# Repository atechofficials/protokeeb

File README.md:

<picture>
 <source media="(prefers-color-scheme: dark)" srcset="Images/protokeeb_logo/protokeeb_logo_white.png">
 <source media="(prefers-color-scheme: light)" srcset="Images/protokeeb_logo/protokeeb_logo_black.png">
 
</picture>

# Protokeeb

### Overview

Protokeeb is a 16-key (4 x 4) keyboard/numpad/macropad/MIDI device designed by A-Tech Officials. It is ideal for those looking to get started with custom keyboards and open-source keyboard firmware. The PCB is based on a Raspberry Pi Pico development board, making it perfect for developers and enthusiasts eager to explore the world of custom keyboards and firmware.

## Features

- Per-key south-facing ARGB (WS2812B-2020) backlight LED.
- All anti-ghosting keys. It's a Mechanical Keyboard. Duh.
- N-Key Rollover
- On-board ESD/EMI protection.
- Rotary Encoder with push button.
- USB Type-C port. Not a feature anymore in 2024. #NoMoreMicroUSB
- Dedicated Bootselect and Reset Button for easy bootloader access.
- Supports various RP2040-based development boards that have similar SMD footprint and pinout to a Raspberry Pi Pico.
- 2MB/4MB flash storage for comprehensive keyboard firmware.
- Compatible with QMK, KMK, and ZMK keyboard firmware.
- Support both sandwich style/layered case or 3D-printed cases.

## Supported Dev Boards

- Raspberry Pi Pico
- Raspberry Pi Pico W
- Waveshare RP2040-Plus

## Getting Started

You can get started with Protokeeb hardware in two ways:

- **Option 1**: Order a fully assembled/soldered PCB from [A-Tech Officials](https://atechofficials.com/protokeeb) (Work-in-progress).
- **Option 2**: Download the Gerber and necessary files to order the PCB from your local or preferred PCB fabrication company and source all required electronic components yourself.

**Option 1** is a straightforward plug-and-play option, as each Protokeeb board comes pre-flashed with QMK firmware and a default keymap, allowing easy customization without worrying about the electronics.

**Option 2** is a DIY approach with detailed instructions provided for almost every step, ideal for those who want to immerse themselves in the learning, development, and customization aspects of custom keyboards.

> [!NOTE]
> Option 2 is not recommended for absolute beginners in electronics, as it requires specific skills and basic electronics knowledge, including proficient SMD soldering skills.

For detailed assembly instructions, follow this guide: [Assembly Instructions](assembly_instructions.md)

## License

This project is licensed under the MIT License. See the [LICENSE](LICENSE) file for details.

## Contributing

Contributions are welcome! Please fork this repository and submit a pull request with your changes.

## Support

For any issues or questions, please open an issue on GitHub.

## Acknowledgements

Thanks to the open-source community for their support and contributions.

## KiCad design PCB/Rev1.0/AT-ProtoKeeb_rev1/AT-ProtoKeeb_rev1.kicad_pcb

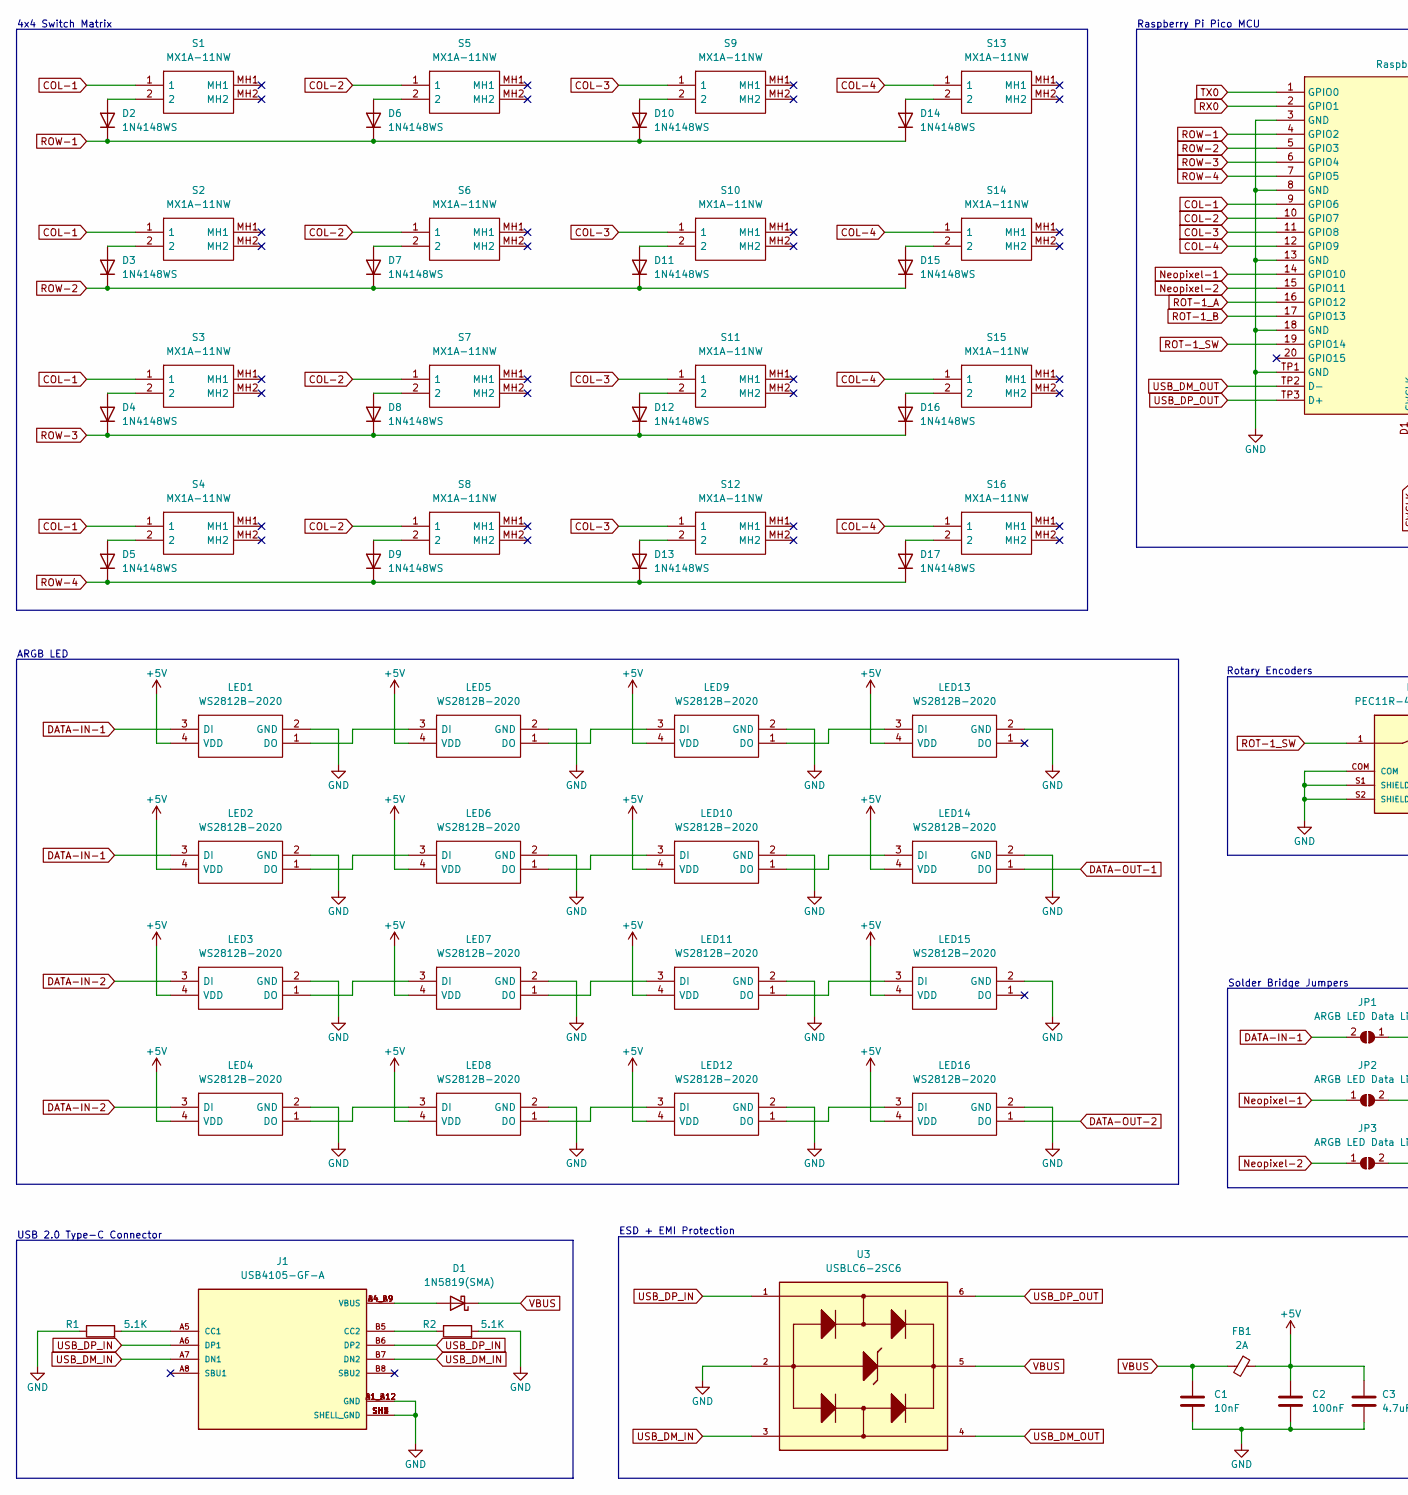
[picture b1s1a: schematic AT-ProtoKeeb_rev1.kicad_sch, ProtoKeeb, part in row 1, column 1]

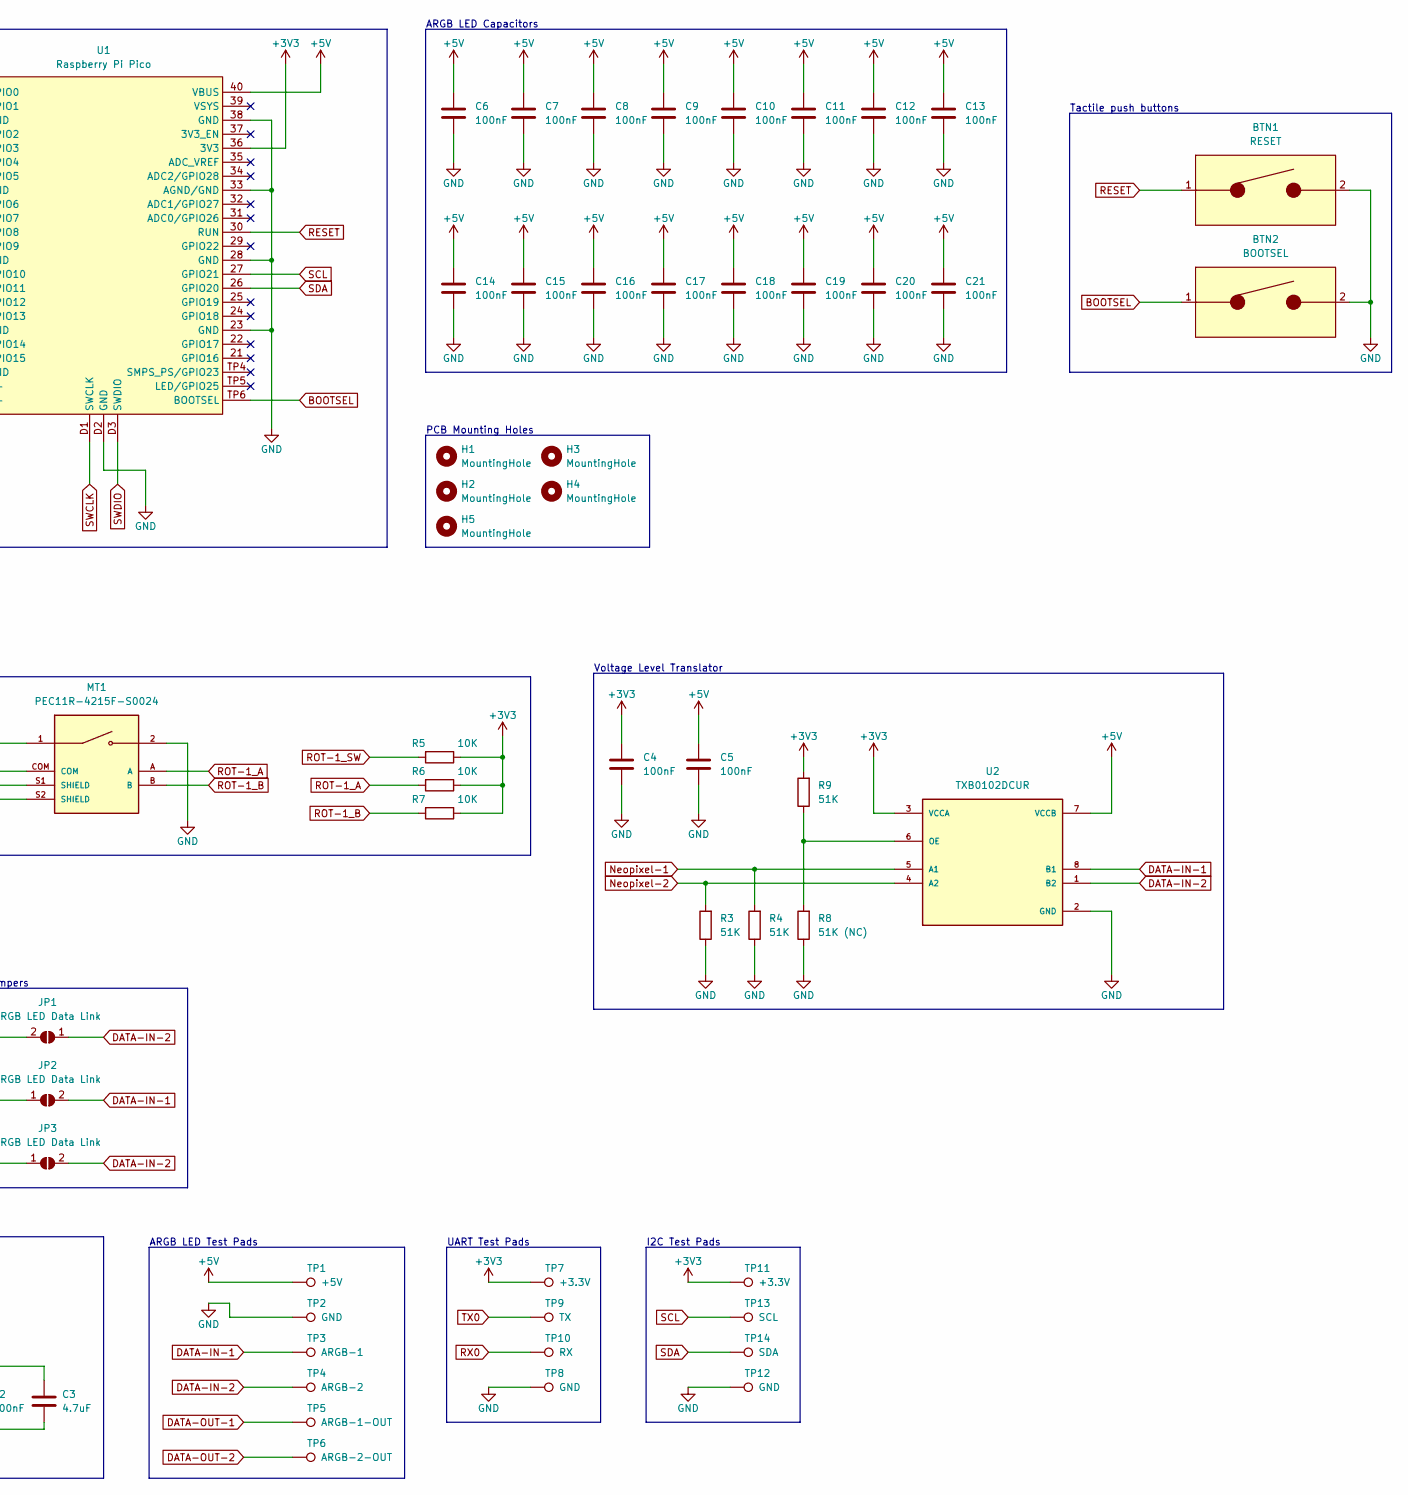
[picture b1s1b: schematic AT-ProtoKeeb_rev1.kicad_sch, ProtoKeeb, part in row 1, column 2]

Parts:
BTN1: RESET; 4982; Mouser Part Number 653-B3U-1000PM
BTN2: BOOTSEL; 4982; Mouser Part Number 653-B3U-1000PM
C1: 10nF; C_0603_1608Metric; Mouser Part Number 603-CC603KRX7R9BB103
C2, C4, C5, C6, C7, C8, C9, C10, C11, C12, C13, C14, C15, C16, C17, C18, C19, C20, C21: 100nF; C_0603_1608Metric; Mouser Part Number 81-GCJ188R71H104KA2D
C3: 4.7uF; C_0603_1608Metric; Mouser Part Number 81-GRM188Z71C475KE1D
D1: 1N5819(SMA); D_SMA; Mouser Part Number 512-SS14
D2, D3, D4, D5, D6, D7, D8, D9, D10, D11, D12, D13, D14, D15, D16, D17: 1N4148WS; D_SOD-323; Mouser Part Number 512-1N4148WS
FB1: 2A; L_0603_1608Metric; Mouser Part Number 810-MPZ1608S221ATA00
H1, H2, H3, H4, H5: MountingHole; MountingHole_2.7mm_M2.5_ISO7380
J1: USB4105-GF-A; GCT_USB4105-GF-A; PARTREV B3; Mouser Part Number 640-USB4105-GF-A
JP1, JP2, JP3: ARGB LED Data Link; SolderJumper-2_P1.3mm_Open_TrianglePad1.0x1.5mm
LED1, LED2, LED3, LED4, LED5, LED6, LED7, LED8, LED9, LED10, LED11, LED12, LED13, LED14, LED15, LED16: WS2812B-2020; WS2812B2020; Manufacturer_Part_Number WS2812B-2020; Mouser Part Number 485-4684
MT1: PEC11R-4215F-S0024; XDCR_PEC11R-4215F-S0024; PARTREV Rev. 09/19; Mouser Part Number 652-PEC11R-4215F-S24
R1, R2: 5.1K; R_0603_1608Metric; Mouser Part Number 603-RC0603FR-075K1L
R3, R4, R9: 51K; R_0603_1608Metric; Mouser Part Number 603-RC0603FR-0751KL
R5, R6, R7: 10K; R_0603_1608Metric; Mouser Part Number 603-RC0603FR-0710KL
R8: 51K (NC); R_0603_1608Metric; Mouser Part Number 603-RC0603FR-0751KL
S1, S2, S3, S4, S5, S6, S7, S8, S9, S10, S11, S12, S13, S14, S15, S16: MX1A-11NW; MX1A11NW; Manufacturer_Part_Number MX1A-11NW; Mouser Part Number 540-MX1A-11NW
TP1: +5V; TestPoint_Pad_D1.0mm
TP2, TP8, TP12: GND; TestPoint_Pad_D1.0mm
TP3: ARGB-1; TestPoint_Pad_D1.0mm
TP4: ARGB-2; TestPoint_Pad_D1.0mm
TP5: ARGB-1-OUT; TestPoint_Pad_D1.0mm
TP6: ARGB-2-OUT; TestPoint_Pad_D1.0mm
TP7, TP11: +3.3V; TestPoint_Pad_D1.0mm
TP9: TX; TestPoint_Pad_D1.0mm
TP10: RX; TestPoint_Pad_D1.0mm
TP13: SCL; TestPoint_Pad_D1.0mm
TP14: SDA; TestPoint_Pad_D1.0mm
U1: Raspberry Pi Pico; RPi_Pico_SMD; PARTREV v3; Mouser Part Number 358-SC0915
U2: TXB0102DCUR; SOP50P310X90-8N; PARTREV D; Mouser Part Number 595-TXB0102DCUR
U3: USBLC6-2SC6; SOT95P280X145-6N; Mouser Part Number 511-USBLC6-2SC6

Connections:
+3V3: C4.1, R5.1, R6.1, R7.1, R9.2, TP7.1, TP11.1, U1.36 (3V3), U2.3 (VCCA)
+5V: C2.1, C3.1, C5.1, C6.1, C7.1, C8.1, C9.1, C10.1, C11.1, C12.1, C13.1, C14.1, C15.1, C16.1, C17.1, C18.1, C19.1, C20.1, C21.1, FB1.1, LED1.4 (VDD), LED2.4 (VDD), LED3.4 (VDD), LED4.4 (VDD), LED5.4 (VDD), LED6.4 (VDD), LED7.4 (VDD), LED8.4 (VDD), LED9.4 (VDD), LED10.4 (VDD), LED11.4 (VDD), LED12.4 (VDD), LED13.4 (VDD), LED14.4 (VDD), LED15.4 (VDD), LED16.4 (VDD), TP1.1, U1.40 (VBUS), U2.7 (VCCB)
BOOTSEL: BTN2.1, U1.TP6 (BOOTSEL)
COL-1: S1.1, S2.1, S3.1, S4.1, U1.9 (GPIO6)
COL-2: S5.1, S6.1, S7.1, S8.1, U1.10 (GPIO7)
COL-3: S9.1, S10.1, S11.1, S12.1, U1.11 (GPIO8)
COL-4: S13.1, S14.1, S15.1, S16.1, U1.12 (GPIO9)
DATA-IN-1: JP1.2 (B), JP2.2 (B), LED1.3 (DI), LED2.3 (DI), TP3.1, U2.8 (B1)
DATA-IN-2: JP1.1 (A), JP3.2 (B), LED3.3 (DI), LED4.3 (DI), TP4.1, U2.1 (B2)
DATA-OUT-1: LED14.1 (DO), TP5.1
DATA-OUT-2: LED16.1 (DO), TP6.1
GND: BTN1.2, BTN2.2, C1.2, C2.2, C3.2, C4.2, C5.2, C6.2, C7.2, C8.2, C9.2, C10.2, C11.2, C12.2, C13.2, C14.2, C15.2, C16.2, C17.2, C18.2, C19.2, C20.2, C21.2, J1.A1_B12 (GND), J1.B1_A12 (GND), J1.SH1 (SHELL_GND), J1.SH2 (SHELL_GND), J1.SH3 (SHELL_GND), J1.SH4 (SHELL_GND), LED1.2 (GND), LED2.2 (GND), LED3.2 (GND), LED4.2 (GND), LED5.2 (GND), LED6.2 (GND), LED7.2 (GND), LED8.2 (GND), LED9.2 (GND), LED10.2 (GND), LED11.2 (GND), LED12.2 (GND), LED13.2 (GND), LED14.2 (GND), LED15.2 (GND), LED16.2 (GND), MT1.2, MT1.COM, MT1.S1 (SHIELD), MT1.S2 (SHIELD), R1.1, R2.2, R3.1, R4.1, R8.1, TP2.1, TP8.1, TP12.1, U1.3 (GND), U1.8 (GND), U1.13 (GND), U1.18 (GND), U1.23 (GND), U1.28 (GND), U1.33 (AGND/GND), U1.38 (GND), U1.D2 (GND), U1.TP1 (GND), U2.2 (GND), U3.2
Neopixel-1: JP2.1 (A), R4.2, U1.14 (GPIO10), U2.5 (A1)
Neopixel-2: JP3.1 (A), R3.2, U1.15 (GPIO11), U2.4 (A2)
unnamed: D1.2 (A), J1.A4_B9 (VBUS), J1.B4_A9 (VBUS)
unnamed: D2.2 (A), S1.2
unnamed: D3.2 (A), S2.2
unnamed: D4.2 (A), S3.2
unnamed: D5.2 (A), S4.2
unnamed: D6.2 (A), S5.2
unnamed: D7.2 (A), S6.2
unnamed: D8.2 (A), S7.2
unnamed: D9.2 (A), S8.2
unnamed: D10.2 (A), S9.2
unnamed: D11.2 (A), S10.2
unnamed: D12.2 (A), S11.2
unnamed: D13.2 (A), S12.2
unnamed: D14.2 (A), S13.2
unnamed: D15.2 (A), S14.2
unnamed: D16.2 (A), S15.2
unnamed: D17.2 (A), S16.2
unnamed: J1.A5 (CC1), R1.2
unnamed: J1.B5 (CC2), R2.1
unnamed: LED1.1 (DO), LED5.3 (DI)
unnamed: LED2.1 (DO), LED6.3 (DI)
unnamed: LED3.1 (DO), LED7.3 (DI)
unnamed: LED4.1 (DO), LED8.3 (DI)
unnamed: LED5.1 (DO), LED9.3 (DI)
unnamed: LED6.1 (DO), LED10.3 (DI)
unnamed: LED10.1 (DO), LED14.3 (DI)
unnamed: LED7.1 (DO), LED11.3 (DI)
unnamed: LED11.1 (DO), LED15.3 (DI)
unnamed: LED8.1 (DO), LED12.3 (DI)
unnamed: LED12.1 (DO), LED16.3 (DI)
unnamed: LED9.1 (DO), LED13.3 (DI)
unnamed: R8.2, R9.1, U2.6 (OE)
RESET: BTN1.1, U1.30 (RUN)
ROT-1_A: MT1.A, R6.2, U1.16 (GPIO12)
ROT-1_B: MT1.B, R7.2, U1.17 (GPIO13)
ROT-1_SW: MT1.1, R5.2, U1.19 (GPIO14)
ROW-1: D2.1 (K), D6.1 (K), D10.1 (K), D14.1 (K), U1.4 (GPIO2)
ROW-2: D3.1 (K), D7.1 (K), D11.1 (K), D15.1 (K), U1.5 (GPIO3)
ROW-3: D4.1 (K), D8.1 (K), D12.1 (K), D16.1 (K), U1.6 (GPIO4)
ROW-4: D5.1 (K), D9.1 (K), D13.1 (K), D17.1 (K), U1.7 (GPIO5)
RX0: TP10.1, U1.2 (GPIO1)
SCL: TP13.1, U1.27 (GPIO21)
SDA: TP14.1, U1.26 (GPIO20)
SWCLK: U1.D1 (SWCLK)
SWDIO: U1.D3 (SWDIO)
TX0: TP9.1, U1.1 (GPIO0)
USB_DM_IN: J1.A7 (DN1), J1.B7 (DN2), U3.3
USB_DM_OUT: U1.TP2 (D-), U3.4
USB_DP_IN: J1.A6 (DP1), J1.B6 (DP2), U3.1
USB_DP_OUT: U1.TP3 (D+), U3.6
VBUS: C1.1, D1.1 (K), FB1.2, U3.5

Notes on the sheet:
Rotary Encoders
Voltage Level Translator
Raspberry Pi Pico MCU
4x4 Switch Matrix
PCB Mounting Holes
Solder Bridge Jumpers
UART Test Pads
ARGB LED Capacitors
ARGB LED
ARGB LED Test Pads
USB 2.0 Type-C Connector
Tactile push buttons
ESD + EMI Protection
I2C Test Pads

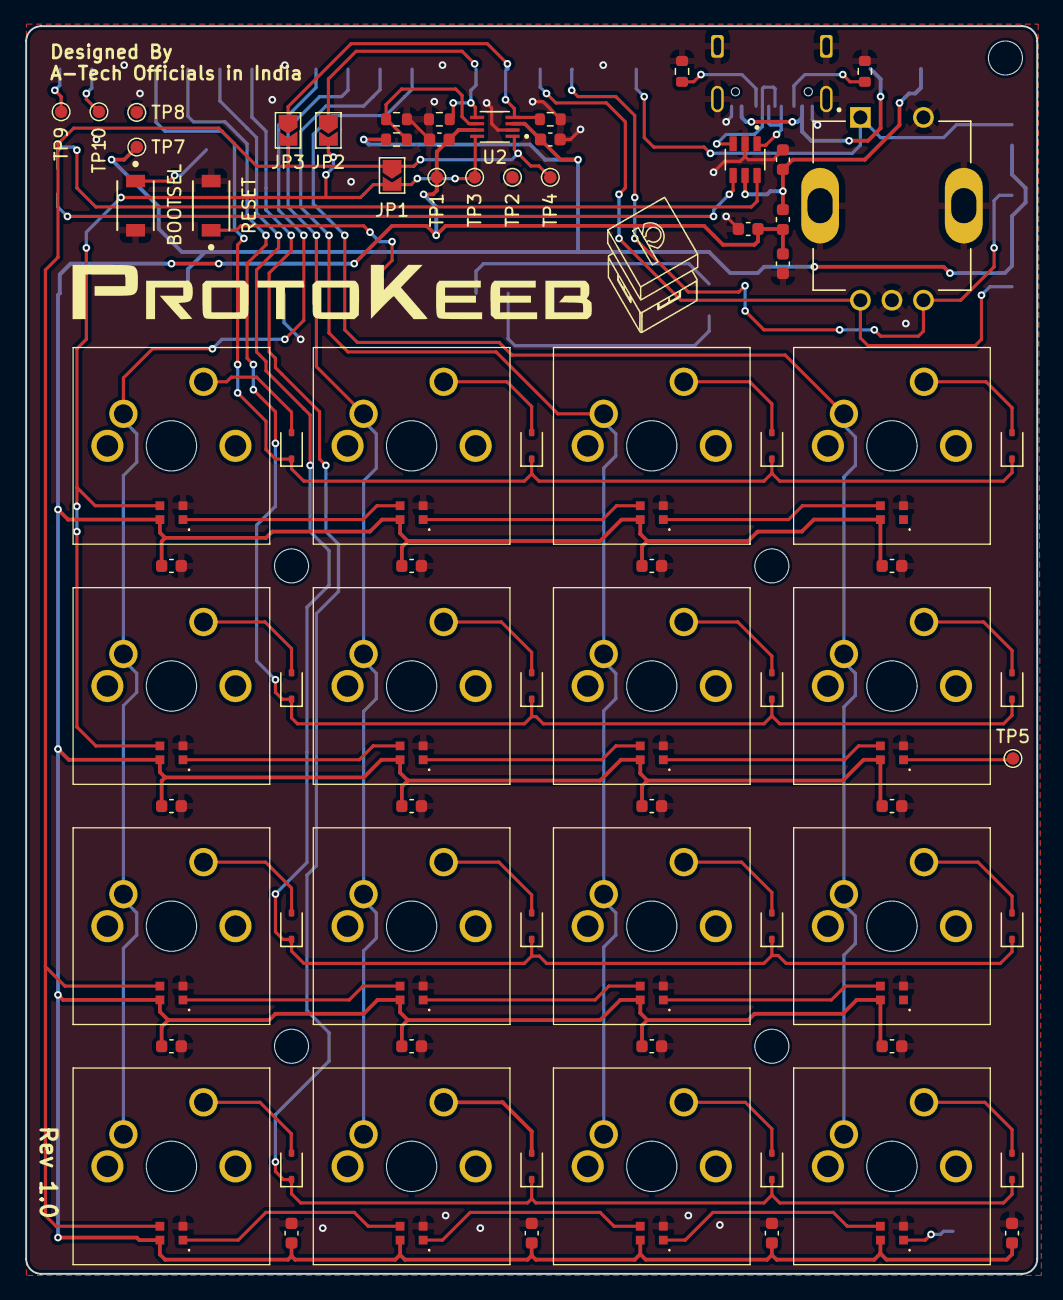
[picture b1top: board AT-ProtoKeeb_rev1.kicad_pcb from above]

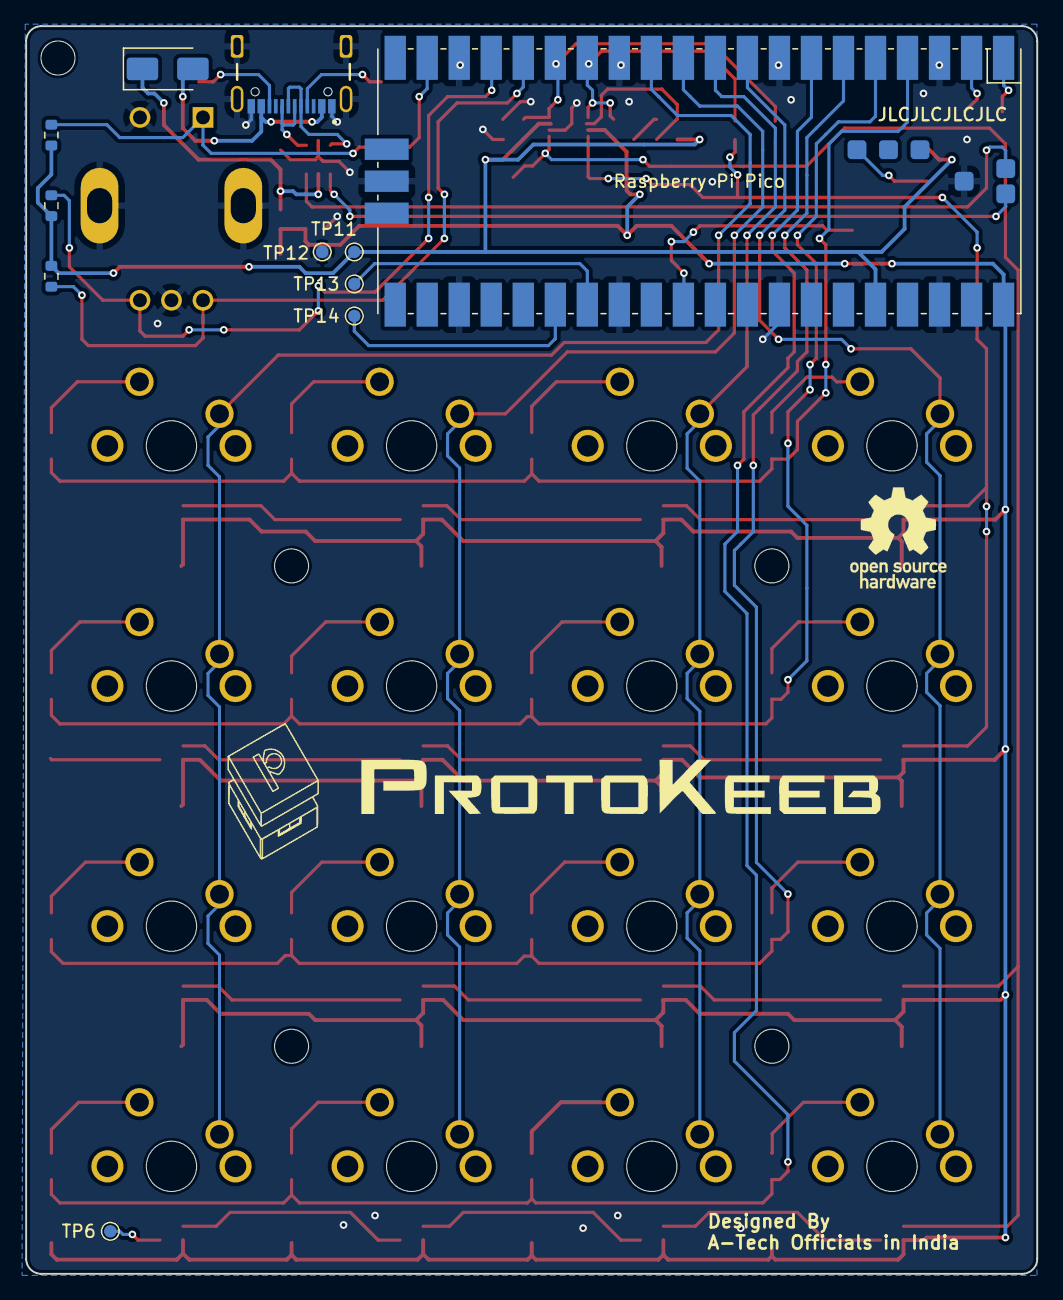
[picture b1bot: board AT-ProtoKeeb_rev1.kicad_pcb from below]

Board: 2 copper layers, 80.2 x 99.0 mm, 109 parts (11 on the bottom side), 63 nets.

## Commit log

2024-02-03 ProtoKeeb LICENSE
2024-04-24 Protokeeb Rev1 Files
2024-04-24 Protokeeb Rev1 QMK Firmware Uploaded
2024-04-24 Protokeeb Via Layout Image Uploaded
2024-04-26 Protokeeb latest QMK Firmware file upload
2024-04-26 Protokeeb readme file updated
2024-06-15 Updated the Readme file content
2024-06-17 Added Assembly Instructions
2024-06-17 minor mistakes rectified in Assembly Instructions
2024-06-17 minor changes in Assembly Instructions
2024-06-19 minor changes and improvements in the Protokeeb Rev1 PCB files
2024-06-20 Minor updates/changes in the Protokeeb rev1 Sandwich Case CAD files
2024-06-20 slight modifications in Protokeeb rev1 Assembly Instruction file
2024-06-24 Added Protokeeb rev1 compiled QMK firmware files for all the available keymaps
2024-06-24 Changed Protokeeb rev1 RGB LED size comparison image
2024-06-25 Added compiled QMK firmware files for Protokeeb rev1 (in .uf2 format) and removed the debug and default_ortho_4x4 keymaps because they are not required anymore. Also, slight changes in the protokeeb_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
2024-06-27 Updated compiled QMK firmware for Protokeeb Rev1 in .uf2 format
2024-07-14 Updated compiled QMK firmware .uf2 files for Protokeeb rev1.
2025-07-04 Added Assembly Instructions for Protokeeb 3D Printed Case, Added Protokeeb 3D Printed Case STL Files, Added 3D Printed Case Images and some modifications to the documentaion.
2025-07-07 Minor changes in the assembly instructions and added some images.
